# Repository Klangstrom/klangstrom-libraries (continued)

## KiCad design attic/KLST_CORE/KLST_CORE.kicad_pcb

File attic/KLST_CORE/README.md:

# KLANGSTROM / KLST_CORE

KLST_CORE is the core audio processing unit:

- featuring *KLANGSTROM* library
- programmable in Arduino IDE via USB ( *DFUse Mode* )
- debugging + communication via *virtual USB Serial Port*

## feature list (20210303)

- STM32H743 MCU with 480MHz, 1 MB RAM, 2MB Flash
- WM8731 Audio Codec with 2× AUDIO DAC + 2× AUDIO ADC ( 24BIT )
- 16× GPIO Pins
- 6× ADC ( 16BIT )
- 2× DAC ( 12BIT )
- 3× UART ( with symetric IDC )
- 3× I2C ( with symetric IDC )
- 3× SPI ( with symetric IDC )
- 1× SD CARD reader
- USB Host
- USB Device ( + Power Supply )
- 3× Rotary Encoder + Push Button
- 2× Push Buttons
- Reset + Boot Flash + Programmer Buttons
- JTAG/SWD Interface ( 10-Pin )
- Eurorack Power Supply ( 12V )
- Eurorack Connectors for 2× AUDIO DAC + 2× AUDIO ADC 
- 3× programmable LEDs + 1× Power LED
- 4× Mounting Holes

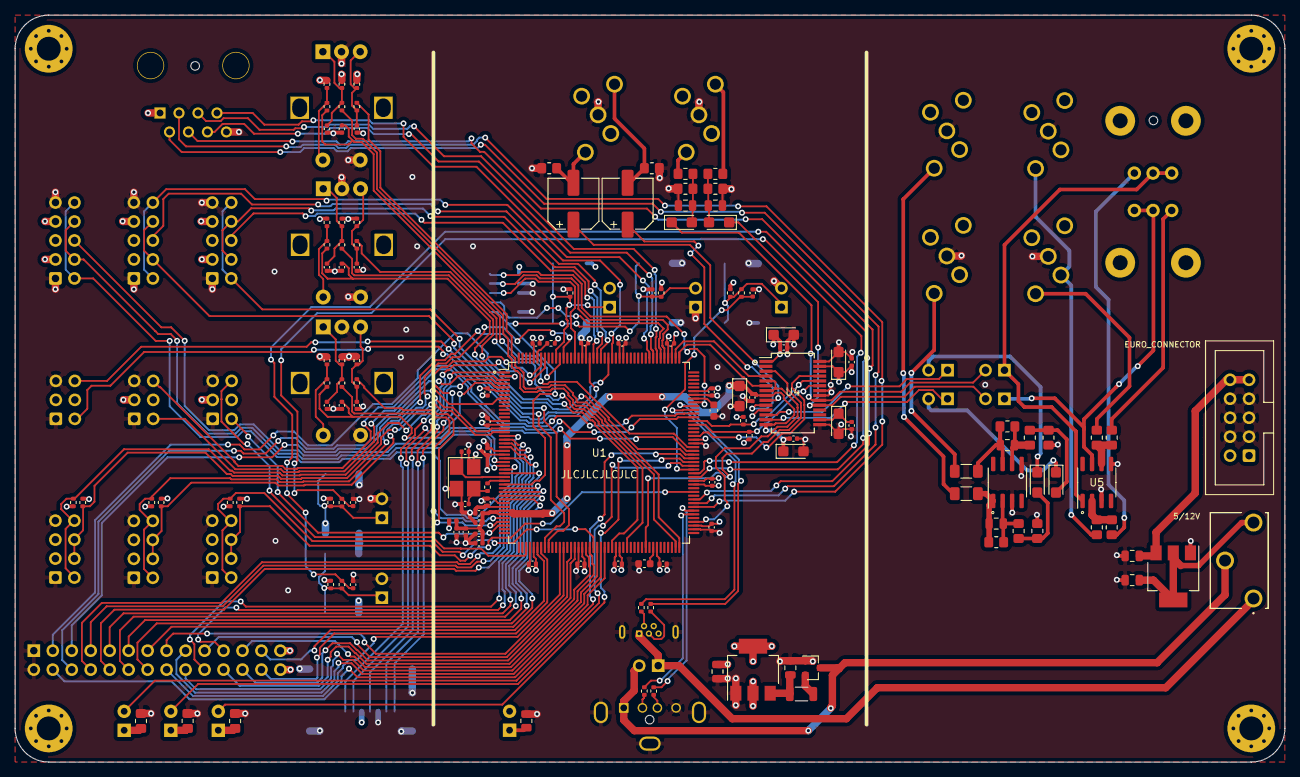
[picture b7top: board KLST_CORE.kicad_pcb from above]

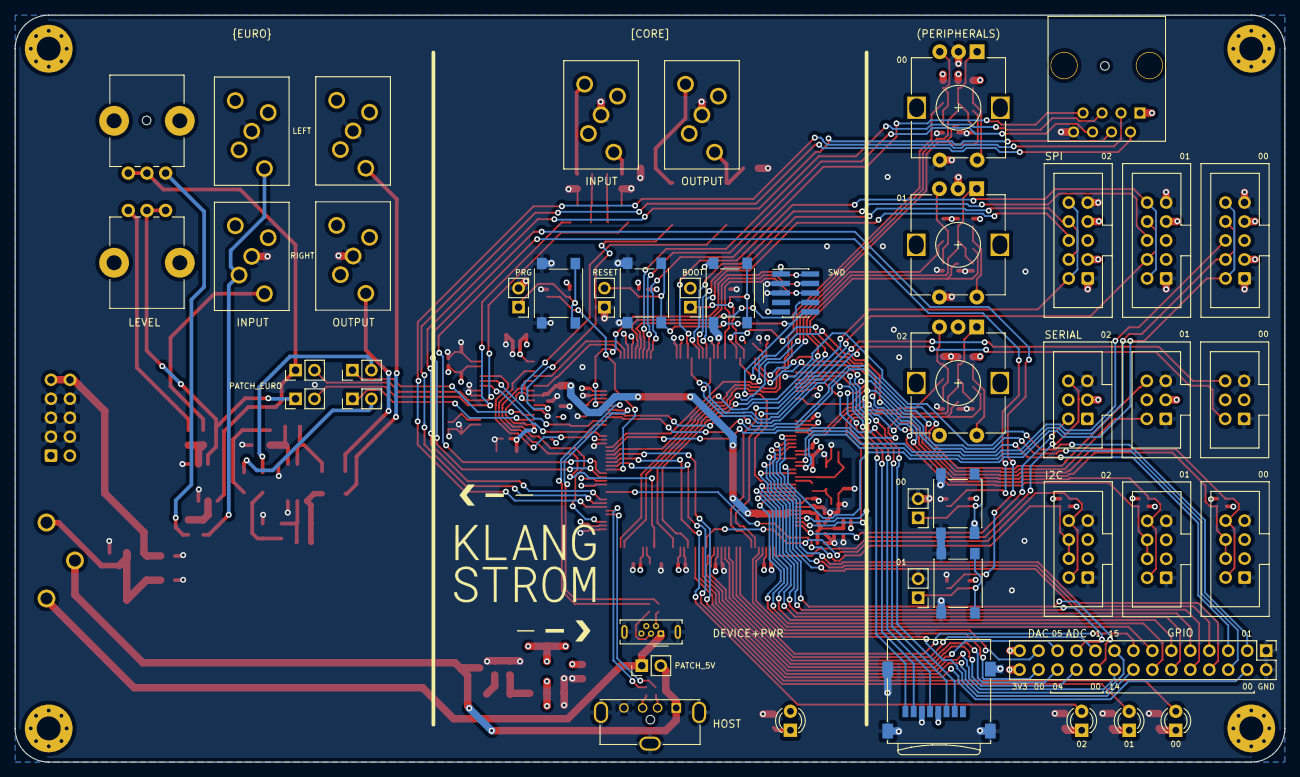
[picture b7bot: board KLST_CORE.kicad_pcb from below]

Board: 4 copper layers, 170.0 x 100.0 mm, 186 parts (46 on the bottom side), 154 nets.

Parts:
C1, C2, C3, C4, C14, C16, C20, C21, C22, C23, C24, C25, C26, C27, C28, C29, C30, C31, C32, C33, C37, C41, C43, C45, C47, C54, C55, C56, C57, C58, C59, C60, C61, C62: 100nF; C_0402_1005Metric
C5, C6, C7, C8: 10uF; C_0805_2012Metric
C9, C10: 12pF; C_0402_1005Metric
C11, C12: 2.2uF; C_0603_1608Metric
C13, C15, C17, C19: 1uF; C_0402_1005Metric
C18: 10nF; C_0402_1005Metric
C34, C35: 220uF; CP_Elec_6.3x5.4
C36, C42, C44, C46, C48, C51, C53: 10uF; CP_EIA-3216-18_Kemet-A
C38, C40: 1uF; CP_EIA-3216-18_Kemet-A
C39, C49: 220pF; C_0805_2012Metric
C50, C52: 18pF; C_0805_2012Metric
D1, D2, D3, D4: LED; LED_D3.0mm
FB1: 600Ω@100MHz; L_1206_3216Metric
H1, H2, H3, H4: MountingHole; MountingHole_3.2mm_M3_Pad_Via
J1: RJ45; RJ45_molex_95503-2884-8P8C_Vertical
J2: Micro_SD_Card; microSD_HC_Wuerth_693072010801
J3: USB_A; USB_A_Molex_105057_Vertical
J4: USB_B_Micro; USB_Micro-B_Wuerth_614105150721_Vertical
J5: GPIO+ANALOG_IO_PINS; PinHeader_2x14_P2.54mm_Vertical
J8: EURORACK_POWER_SUPPLY; IDC-Header_2x05_P2.54mm_Vertical
J9: ARM_JTAG_SWD; PinHeader_2x05_P1.27mm_Vertical_SMD
J10: HEADPHONE_OUT; STX36805NB
J11: LINE_IN; STX36805NB
J12: EURO_IN_RIGHT; STX36805NB
J13: EURO_OUT_RIGHT; STX36805NB
J14: EURO_IN_LEFT; STX36805NB
J15: EURO_OUT_LEFT; STX36805NB
J16: SPI_00; IDC-Header_2x05_P2.54mm_Vertical
J17: UART_00; IDC-Header_2x03_P2.54mm_Vertical
J18: I2C_00; IDC-Header_2x04_P2.54mm_Vertical
J19: UART_01; IDC-Header_2x03_P2.54mm_Vertical
J20: SPI_01; IDC-Header_2x05_P2.54mm_Vertical
J21: I2C_01; IDC-Header_2x04_P2.54mm_Vertical
J22: UART_02; IDC-Header_2x03_P2.54mm_Vertical
J23: SPI_02; IDC-Header_2x05_P2.54mm_Vertical
J24: I2C_02; IDC-Header_2x04_P2.54mm_Vertical
JP1: BUTTON_BOOT_FLASH_EXT; PinHeader_1x02_P2.54mm_Vertical
JP2: BUTTON_RESET_EXT; PinHeader_1x02_P2.54mm_Vertical
JP3: BUTTON_USER_00_EXT; PinHeader_1x02_P2.54mm_Vertical
JP4: BUTTON_USER_01_EXT; PinHeader_1x02_P2.54mm_Vertical
JP5: BUTTON_PROGRAMMER_EXT; PinHeader_1x02_P2.54mm_Vertical
JP6: USB_POWER_INPUT; PinHeader_1x02_P2.54mm_Vertical
JP7: JUMPER_SIGNAL_IN_RIGHT; PinHeader_1x02_P2.54mm_Vertical
JP8: JUMPER_SIGNAL_OUT_RIGHT; PinHeader_1x02_P2.54mm_Vertical
JP9: JUMPER_SIGNAL_IN_LEFT; PinHeader_1x02_P2.54mm_Vertical
JP10: JUMPER_SIGNAL_OUT_LEFT; PinHeader_1x02_P2.54mm_Vertical
L1: 39nH; L_0402_1005Metric
Q1: AO3401A; SOT-23
R1, R2, R3, R4: 22R; R_0402_1005Metric
R5, R6, R7: 1K; R_0805_2012Metric_Pad1.20x1.40mm_HandSolder
R8: 1K; R_0805_2012Metric
R9, R10, R11, R12, R16, R39, R41, R42, R43, R44, R45, R47, R48, R49, R50, R51, R53, R54, R55, R56: 10K; R_0402_1005Metric
R13, R14, R15, R40, R46, R52: 1K; R_0402_1005Metric
R17: 10R; R_0402_1005Metric
R18: 5.6K; R_0402_1005Metric
R19, R20, R57, R58, R59, R60, R61, R62: 2.2K; R_0402_1005Metric
R21, R22: 47K; R_0805_2012Metric_Pad1.20x1.40mm_HandSolder
R23, R24, R25, R26, R30, R36: 5.6K; R_0805_2012Metric_Pad1.20x1.40mm_HandSolder
R27, R33: 3.3K; R_0805_2012Metric_Pad1.20x1.40mm_HandSolder
R28, R32, R34, R38: 39K; R_0805_2012Metric_Pad1.20x1.40mm_HandSolder
R29, R35: 22K; R_0805_2012Metric_Pad1.20x1.40mm_HandSolder
R31, R37: 1K; R_1206_3216Metric_Pad1.30x1.75mm_HandSolder
RV1, RV2: 50K; Potentiometer_Bourns_PTV09A-1_Single_Vertical
SW1: BUTTON_BOOT_FLASH; SW_Push_1P1T_NO_6x6mm_H9.5mm
SW2: BUTTON_RESET; SW_Push_1P1T_NO_6x6mm_H9.5mm
SW3: BUTTON_USER_00; SW_Push_1P1T_NO_6x6mm_H9.5mm
SW4: BUTTON_USER_01; SW_Push_1P1T_NO_6x6mm_H9.5mm
SW5: BUTTON_PROGRAMMER; SW_Push_1P1T_NO_6x6mm_H9.5mm
SW6: POWER_SELECTOR; G1070513
SW7, SW8, SW9: ENCODER; RotaryEncoder_Alps_EC12E-Switch_Vertical_H20mm
U1: STM32H743IITx; LQFP-176_24x24mm_P0.5mm
U2: AMS1117-5.0; SOT-223-3_TabPin2
U3: AMS1117-3.3; SOT-223-3_TabPin2
U4: WM8731SEDS; SSOP-28_5.3x10.2mm_P0.65mm
U5, U6: TL072; SOIC-8_3.9x4.9mm_P1.27mm
X1: LOGO; KLST_CORE--graphics
Y1: 16MHz; Crystal_SMD_3225-4Pin_3.2x2.5mm_HandSoldering

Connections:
+3.3VA: C13.1, C14.1, C15.1, C16.1, C17.1, C18.1, C41.2, C42.1, C43.2, C44.1, L1.2, U1.38, U1.39, U4.8, U4.14
+3V3: C8.1, C19.1, C20.1, C21.1, C22.1, C23.1, C24.1, C25.1, C26.1, C27.1, C28.1, C29.1, C30.1, C31.1, C32.1, C33.1, C45.2, C46.1, C47.2, C48.1, D4.2, J1.1, J2.4, J5.27, J5.28, J9.1, J16.3, J16.7, J17.3, J18.3, J18.5, J19.3, J20.3, J20.7, J21.3, J21.5, J22.3, J23.3, J23.7, J24.3, J24.5, JP1.2, L1.1, R9.2, R10.2, R11.2, R12.2, R18.1, R19.1, R20.1, R39.2, R41.1, R42.1, R45.2, R47.1, R48.1, R51.2, R53.1, R54.1, R57.1, R58.1, R59.1, R60.1, R61.1, R62.1, SW1.2, U1.6, U1.15, U1.23, U1.36, U1.49, U1.62, U1.72, U1.82, U1.91, U1.103, U1.114, U1.127, U1.136, U1.149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
+5V: J3.1, JP6.2, Q1.3, SW6.2
+12V: C5.1, J8.9, J8.10, U2.3
/ADC_00: J5.20, U1.21
/ADC_01: J5.19, U1.59
/ADC_02: J5.22, U1.63
/ADC_03: J5.21, U1.24
/ADC_04: J5.24, U1.60
/ADC_05: J5.23, U1.64
/AUDIOCODEC_I2C_SCL: R19.2, U1.119, U4.24
/AUDIOCODEC_I2C_SDA: R20.2, U1.118, U4.23
/AUDIOCODEC_I2S_CK: U1.79, U4.3
/AUDIOCODEC_I2S_MCK: U1.115, U4.25
/AUDIOCODEC_I2S_SDI: U1.133, U4.6
/AUDIOCODEC_I2S_SDO: U1.134, U4.4
/AUDIOCODEC_I2S_WS: U1.92, U4.5, U4.7
/BOOT_FLASH: JP1.1, R16.2, SW1.1, U1.166
/BUTTON_PROGRAMMER: C3.1, R15.1, U1.106
/BUTTON_USER_00: C1.2, R13.1, U1.105
/BUTTON_USER_01: C2.1, R14.1, U1.104
/DAC_00: J5.26, U1.51
/DAC_01: J5.25, U1.50
/ENCODER_00_A: R49.2, U1.87
/ENCODER_00_B: R50.1, U1.88
/ENCODER_00_BUTTON: C57.1, R46.1, U1.112
/ENCODER_01_A: R43.2, U1.70
/ENCODER_01_B: R44.1, U1.74
/ENCODER_01_BUTTON: C54.1, R40.1, U1.110
/ENCODER_02_A: R55.2, U1.40
/ENCODER_02_B: R56.1, U1.41
/ENCODER_02_BUTTON: C60.1, R52.1, U1.111
/GPIO_00: J5.4, U1.68
/GPIO_01: J5.3, U1.2
/GPIO_02: J5.6, U1.3
/GPIO_03: J5.5, U1.8
/GPIO_04: J5.8, U1.18
/GPIO_05: J5.7, U1.19
/GPIO_06: J5.10, U1.20
/GPIO_07: J5.9, U1.28
/GPIO_08: J5.12, U1.32
/GPIO_09: J5.11, U1.33
/GPIO_10: J5.14, U1.34
/GPIO_11: J5.13, U1.35
/GPIO_12: J5.16, U1.56
/GPIO_13: J5.15, U1.57
/GPIO_14: J5.18, U1.66
/GPIO_15: J5.17, U1.67
/I2C_00_SCL: J18.4, J18.6, R57.2, U1.17
/I2C_00_SDA: J18.2, J18.8, R58.2, U1.16
/I2C_01_SCL: J21.4, J21.6, R59.2, U1.164
/I2C_01_SDA: J21.2, J21.8, R60.2, U1.165
/I2C_02_SCL: J24.4, J24.6, R61.2, U1.100
/I2C_02_SDA: J24.2, J24.8, R62.2, U1.65
/LED_00: D1.2, U1.109
/LED_01: D2.2, U1.107
/LED_02: D3.2, U1.108
/PDR_ON: R18.2, U1.171
/RCC_OSC_IN: C9.2, U1.29, Y1.1
/RCC_OSC_OUT: R17.1, U1.30
/RJ45_GPIO: J1.4, U1.98
/RJ45_SPI_MISO: J1.6, U1.140
/RJ45_SPI_MOSI: J1.7, U1.141
/RJ45_SPI_SCK: J1.5, U1.139
/RJ45_UART_RX: J1.2, U1.97
/RJ45_UART_TX: J1.3, U1.96
/SDCARD_CS: J2.2, U1.169
/SDCARD_DETECT_SDIO: J2.8, U1.170
/SDCARD_MISO: J2.7, U1.4
/SDCARD_MOSI: J2.3, U1.5
/SDCARD_SCK: J2.5, U1.1
/SPI_00_MISO: J16.4, J16.8, U1.26
/SPI_00_MOSI: J16.2, J16.10, U1.27
/SPI_00_SCK: J16.6, U1.25
/SPI_01_MISO: J20.4, J20.8, U1.52
/SPI_01_MOSI: J20.2, J20.10, U1.151
/SPI_01_SCK: J20.6, U1.154
/SPI_02_MISO: J23.4, J23.8, U1.155
/SPI_02_MOSI: J23.2, J23.10, U1.53
/SPI_02_SCK: J23.6, U1.156
/SWD_NRST: C4.2, J9.10, JP2.2, R12.1, SW2.2, U1.31
/SWD_SWCLK: J9.4, U1.137
/SWD_SWDIO: J9.2, U1.124
/SWD_SWI: J9.8, U1.138
/SWD_SWO: J9.6, U1.161
/USART_00_RX: J17.6, U1.152
/USART_00_TX: J17.2, U1.157
/USART_01_RX: J19.6, U1.121
/USART_01_TX: J19.2, U1.120
/USART_02_RX: J22.6, U1.47
/USART_02_TX: J22.2, U1.42
/USB_DEVICE_D+: R2.1, U1.123
/USB_DEVICE_D-: R4.1, U1.122
/USB_HOST_D+: R1.1, U1.95
/USB_HOST_D-: R3.1, U1.94
/USB_POWER_INPUT_5V+: J4.1, JP6.1, SW6.1
/VCAP1: C11.1, U1.81
/VCAP2: C12.1, U1.125
/audio_codec_WM8731/AUDIO_IN_LEFT: J11.T, R23.2
/audio_codec_WM8731/AUDIO_IN_RIGHT: J11.R, R25.2
/audio_codec_WM8731/AUDIO_OUT_LEFT: C34.2, J10.T, R21.1
/audio_codec_WM8731/AUDIO_OUT_RIGHT: C35.2, J10.R, R22.1
/audio_codec_WM8731/HEADPHONE_OUT_LEFT: C34.1, U4.9
/audio_codec_WM8731/HEADPHONE_OUT_RIGHT: C35.1, U4.10
/audio_codec_WM8731/SIGNAL_IN_LEFT: C38.1, JP9.2, U4.20
/audio_codec_WM8731/SIGNAL_IN_RIGHT: C40.1, JP7.2, U4.19
/audio_codec_WM8731/SIGNAL_OUT_LEFT: JP10.1, U4.12
/audio_codec_WM8731/SIGNAL_OUT_RIGHT: JP8.1, U4.13
GND: C1.1, C2.2, C3.2, C4.1, C5.2, C6.2, C7.2, C8.2, C9.1, C10.2, C11.2, C12.2, C13.2, C14.2, C15.2, C16.2, C17.2, C18.2, C19.2, C20.2, C21.2, C22.2, C23.2, C24.2, C25.2, C26.2, C27.2, C28.2, C29.2, C30.2, C31.2, C32.2, C33.2, C36.2, C37.2, C39.1, C41.1, C42.2, C43.1, C44.2, C45.1, C46.2, C47.1, C48.2, C49.1, C54.2, C55.2, C56.2, C57.2, C58.2, C59.2, C60.2, C61.2, C62.2, J1.8, J2.6, J2.9, J3.4, J3.5, J4.5, J4.6, J5.1, J5.2, J8.3, J8.4, J8.5, J8.6, J8.7, J8.8, J9.3, J9.5, J9.9, J10.S, J11.S, J12.S, J13.S, J14.S, J15.S, J16.1, J16.9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
unnamed: C6.1, SW6.3, U2.2
unnamed: C7.1, FB1.1, U3.3
unnamed: C10.1, R17.2, Y1.3
unnamed: C36.1, C37.1, U4.16
unnamed: C38.2, C39.2, R23.1, R24.1
unnamed: C40.2, C49.2, R25.1, R26.1
unnamed: C50.1, R28.2, R31.1, U6.7
unnamed: C50.2, R28.1, R30.2, U6.6
unnamed: C51.1, JP8.2
unnamed: C51.2, R30.1, R32.1
unnamed: C52.1, R34.1, R37.1, U6.1
unnamed: C52.2, R34.2, R36.2, U6.2
unnamed: C53.1, JP10.2
unnamed: C53.2, R36.1, R38.1
unnamed: C55.1, R42.2, R43.1, SW7.A
unnamed: C56.1, R41.2, R44.2, SW7.B
unnamed: C58.1, R48.2, R49.1, SW8.A
unnamed: C59.1, R47.2, R50.2, SW8.B
unnamed: C61.1, R54.2, R55.1, SW9.A
unnamed: C62.1, R53.2, R56.2, SW9.B
unnamed: D1.1, R5.2
unnamed: D2.1, R6.2
unnamed: D3.1, R7.2
unnamed: D4.1, R8.2
unnamed: FB1.2, Q1.2
unnamed: J3.2, R3.2
unnamed: J3.3, R1.2
unnamed: J4.2, R4.2
unnamed: J4.3, R2.2
unnamed: J12.T, R29.2
unnamed: J12.TN, J14.T, R35.2
unnamed: J13.T, R31.2
unnamed: J15.T, R37.2
unnamed: JP3.1, R9.1, R13.2, SW3.2
unnamed: JP4.1, R10.1, R14.2, SW4.2
unnamed: JP5.1, R11.1, R15.2, SW5.2
unnamed: JP7.1, RV1.2, RV1.3, U5.7
unnamed: JP9.1, RV2.2, RV2.3, U5.1
unnamed: R27.1, R29.1, U5.6
unnamed: R27.2, RV1.1
unnamed: R33.1, R35.1, U5.2
unnamed: R33.2, RV2.1
unnamed: R39.1, R40.2, SW7.S1
unnamed: R45.1, R46.2, SW8.S1
unnamed: R51.1, R52.2, SW9.S1

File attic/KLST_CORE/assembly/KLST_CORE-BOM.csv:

Comment,Designator,Footprint,LCSC
"2.2uF","C11,C12","Capacitor_SMD:C_0603_1608Metric","C23630"
"1uF","C13,C15,C17,C19","Capacitor_SMD:C_0402_1005Metric","C52923"
"100nF","C1,C2,C3,C4,C14,C16,C20,C21,C22,C23,C24,C25,C26,C27,C28,C29,C30,C31,C32,C33,C37,C41,C43,C45,C47,C54,C55,C56,C57,C58,C59,C60,C61,C62","Capacitor_SMD:C_0402_1005Metric","C1525"
"10nF","C18","Capacitor_SMD:C_0402_1005Metric","C15195"
"220uF","C34,C35","Capacitor_SMD:CP_Elec_6.3x5.4","C3345"
"10uF","C36,C42,C44,C46,C48,C51,C53","Capacitor_Tantalum_SMD:CP_EIA-3216-18_Kemet-A","C7171"
"1uF","C38,C40","Capacitor_Tantalum_SMD:CP_EIA-3216-18_Kemet-A","C7175"
"220pF","C39,C49","Capacitor_SMD:C_0805_2012Metric","C53172"
"18pF","C50,C52","Capacitor_SMD:C_0805_2012Metric","C1797"
"10uF","C5,C6,C7,C8","Capacitor_SMD:C_0805_2012Metric","C15850"
"12pF","C9,C10","Capacitor_SMD:C_0402_1005Metric","C1547"
"LED","D1,D2,D3,D4","LED_THT:LED_D3.0mm","C34499"
"600Ω@100MHz","FB1","Inductor_SMD:L_1206_3216Metric","C73732"
"MountingHole","H1,H2,H3,H4","MountingHole:MountingHole_3.2mm_M3_Pad_Via",""
"RJ45","J1","Connector_RJ:RJ45_molex_95503-2884-8P8C_Vertical",""
"HEADPHONE_OUT","J10","KLST_CORE:STX36805NB",""
"LINE_IN","J11","KLST_CORE:STX36805NB",""
"EURO_IN_RIGHT","J12","KLST_CORE:STX36805NB",""
"EURO_OUT_RIGHT","J13","KLST_CORE:STX36805NB",""
"EURO_IN_LEFT","J14","KLST_CORE:STX36805NB",""
"EURO_OUT_LEFT","J15","KLST_CORE:STX36805NB",""
"SPI_00","J16","Connector_IDC:IDC-Header_2x05_P2.54mm_Vertical",""
"UART_00","J17","Connector_IDC:IDC-Header_2x03_P2.54mm_Vertical",""
"I2C_00","J18","Connector_IDC:IDC-Header_2x04_P2.54mm_Vertical",""
"UART_01","J19","Connector_IDC:IDC-Header_2x03_P2.54mm_Vertical",""
"Micro_SD_Card","J2","Connector_Card:microSD_HC_Wuerth_693072010801",""
"SPI_01","J20","Connector_IDC:IDC-Header_2x05_P2.54mm_Vertical",""
"I2C_01","J21","Connector_IDC:IDC-Header_2x04_P2.54mm_Vertical",""
"UART_02","J22","Connector_IDC:IDC-Header_2x03_P2.54mm_Vertical",""
"SPI_02","J23","Connector_IDC:IDC-Header_2x05_P2.54mm_Vertical",""
"I2C_02","J24","Connector_IDC:IDC-Header_2x04_P2.54mm_Vertical",""
"USB_A","J3","Connector_USB:USB_A_Molex_105057_Vertical",""
"USB_B_Micro","J4","Connector_USB:USB_Micro-B_Wuerth_614105150721_Vertical",""
"GPIO+ANALOG_IO_PINS","J5","Connector_PinHeader_2.54mm:PinHeader_2x14_P2.54mm_Vertical",""
"EURORACK_POWER_SUPPLY","J8","Connector_IDC:IDC-Header_2x05_P2.54mm_Vertical",""
"ARM_JTAG_SWD","J9","Connector_PinHeader_1.27mm:PinHeader_2x05_P1.27mm_Vertical_SMD",""
"BUTTON_BOOT_FLASH_EXT","JP1","Connector_PinHeader_2.54mm:PinHeader_1x02_P2.54mm_Vertical",""
"JUMPER_SIGNAL_OUT_LEFT","JP10","Connector_PinHeader_2.54mm:PinHeader_1x02_P2.54mm_Vertical",""
"BUTTON_RESET_EXT","JP2","Connector_PinHeader_2.54mm:PinHeader_1x02_P2.54mm_Vertical",""
"BUTTON_USER_00_EXT","JP3","Connector_PinHeader_2.54mm:PinHeader_1x02_P2.54mm_Vertical",""
"BUTTON_USER_01_EXT","JP4","Connector_PinHeader_2.54mm:PinHeader_1x02_P2.54mm_Vertical",""
"BUTTON_PROGRAMMER_EXT","JP5","Connector_PinHeader_2.54mm:PinHeader_1x02_P2.54mm_Vertical",""
"USB_POWER_INPUT","JP6","Connector_PinHeader_2.54mm:PinHeader_1x02_P2.54mm_Vertical",""
"JUMPER_SIGNAL_IN_RIGHT","JP7","Connector_PinHeader_2.54mm:PinHeader_1x02_P2.54mm_Vertical",""
"JUMPER_SIGNAL_OUT_RIGHT","JP8","Connector_PinHeader_2.54mm:PinHeader_1x02_P2.54mm_Vertical",""
"JUMPER_SIGNAL_IN_LEFT","JP9","Connector_PinHeader_2.54mm:PinHeader_1x02_P2.54mm_Vertical",""
"39nH","L1","Inductor_SMD:L_0402_1005Metric","C26443"
"AO3401A","Q1","Package_TO_SOT_SMD:SOT-23","C15127"
"10K","R9,R10,R11,R12,R16,R39,R41,R42,R43,R44,R45,R47,R48,R49,R50,R51,R53,R54,R55,R56","Resistor_SMD:R_0402_1005Metric","C25744"
"1K","R13,R14,R15,R40,R46,R52","Resistor_SMD:R_0402_1005Metric","C11702"
"10R","R17","Resistor_SMD:R_0402_1005Metric","C25077"
"5.6K","R18","Resistor_SMD:R_0402_1005Metric","C25908"
"2.2K","R19,R20,R57,R58,R59,R60,R61,R62","Resistor_SMD:R_0402_1005Metric","C25879"
"47K","R21,R22","Resistor_SMD:R_0805_2012Metric_Pad1.20x1.40mm_HandSolder","C17713"
"5.6K","R23,R24,R25,R26,R30,R36","Resistor_SMD:R_0805_2012Metric_Pad1.20x1.40mm_HandSolder","C4382"
"22K","R29,R35","Resistor_SMD:R_0805_2012Metric_Pad1.20x1.40mm_HandSolder","C17560"
"3.3K","R27,R33","Resistor_SMD:R_0805_2012Metric_Pad1.20x1.40mm_HandSolder","C26010"
"1K","R31,R37","Resistor_SMD:R_1206_3216Metric_Pad1.30x1.75mm_HandSolder","C4410"
"39K","R28,R32,R34,R38","Resistor_SMD:R_0805_2012Metric_Pad1.20x1.40mm_HandSolder","C25826"
"22R","R1,R2,R3,R4","Resistor_SMD:R_0402_1005Metric","C25092"
"1K","R5,R6,R7","Resistor_SMD:R_0805_2012Metric_Pad1.20x1.40mm_HandSolder","C17513"
"1K","R8","Resistor_SMD:R_0805_2012Metric","C17513"
"50K","RV1,RV2","Potentiometer_THT:Potentiometer_Bourns_PTV09A-1_Single_Vertical",""
"BUTTON_BOOT_FLASH","SW1","Button_Switch_SMD:SW_Push_1P1T_NO_6x6mm_H9.5mm",""
"BUTTON_RESET","SW2","Button_Switch_SMD:SW_Push_1P1T_NO_6x6mm_H9.5mm",""
"BUTTON_USER_00","SW3","Button_Switch_SMD:SW_Push_1P1T_NO_6x6mm_H9.5mm",""
"BUTTON_USER_01","SW4","Button_Switch_SMD:SW_Push_1P1T_NO_6x6mm_H9.5mm",""
"BUTTON_PROGRAMMER","SW5","Button_Switch_SMD:SW_Push_1P1T_NO_6x6mm_H9.5mm",""
"POWER_SELECTOR","SW6","KLST_CORE:G1070513",""
"ENCODER","SW7,SW8,SW9","Rotary_Encoder:RotaryEncoder_Alps_EC12E-Switch_Vertical_H20mm",""
"STM32H743IITx","U1","Package_QFP:LQFP-176_24x24mm_P0.5mm","C89597"
"AMS1117-5.0","U2","Package_TO_SOT_SMD:SOT-223-3_TabPin2","C6187"
"AMS1117-3.3","U3","Package_TO_SOT_SMD:SOT-223-3_TabPin2","C6186"
"WM8731SEDS","U4","Package_SO:SSOP-28_5.3x10.2mm_P0.65mm","C323837"
"TL072","U5,U6","Package_SO:SOIC-8_3.9x4.9mm_P1.27mm","C6961"
"KLST_CORE--graphics","X1","KLST_CORE:KLST_CORE--graphics",""
"16MHz","Y1","Crystal:Crystal_SMD_3225-4Pin_3.2x2.5mm_HandSoldering","C13738"

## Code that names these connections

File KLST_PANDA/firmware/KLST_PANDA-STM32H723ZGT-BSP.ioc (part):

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Mcu.Name=STM32H723ZGTx
Mcu.Package=LQFP144
Mcu.UserName=STM32H723ZGTx
PA0.GPIOParameters=GPIO_Label
PA0.GPIO_Label=_ENCODER_01_A
PA0.Signal=S_TIM2_CH1_ETR
PA1.GPIOParameters=GPIO_Label
PA1.GPIO_Label=_ENCODER_01_B
PA1.Signal=S_TIM2_CH2
PA10.GPIOParameters=GPIO_Label
PA10.GPIO_Label=_ENCODER_00_BUTTON
PA10.Signal=S_TIM1_CH3
PA11.GPIOParameters=GPIO_Label
PA11.GPIO_Label=_USB_DEVICE_HOST_MINUS
PA11.Mode=Host_FS
PA11.Signal=USB_OTG_HS_DM
PA12.GPIOParameters=GPIO_Label
PA12.GPIO_Label=_USB_DEVICE_HOST_PLUS
PA12.Mode=Host_FS
PA12.Signal=USB_OTG_HS_DP
PA13(JTMS/SWDIO).GPIOParameters=GPIO_Label
PA13(JTMS/SWDIO).GPIO_Label=_SWD_IO
PA13(JTMS/SWDIO).Mode=Trace_Asynchronous_SW
PA13(JTMS/SWDIO).Signal=DEBUG_JTMS-SWDIO
PA14(JTCK/SWCLK).GPIOParameters=GPIO_Label
PA14(JTCK/SWCLK).GPIO_Label=_SWD_CLK
PA14(JTCK/SWCLK).Mode=Trace_Asynchronous_SW
PA14(JTCK/SWCLK).Signal=DEBUG_JTCK-SWCLK
PA15(JTDI).GPIOParameters=GPIO_Speed,GPIO_Label
PA15(JTDI).GPIO_Label=_DISPLAY_LTDC_R3
PA15(JTDI).GPIO_Speed=GPIO_SPEED_FREQ_VERY_HIGH
PA15(JTDI).Mode=RGB888
PA15(JTDI).Signal=LTDC_R3
PA2.GPIOParameters=GPIO_Speed,GPIO_Label
PA2.GPIO_Label=_DISPLAY_LTDC_R1
PA2.GPIO_Speed=GPIO_SPEED_FREQ_VERY_HIGH
PA2.Mode=RGB888
PA2.Signal=LTDC_R1
PA3.GPIOParameters=GPIO_Label
PA3.GPIO_Label=SERIAL_USR_RX
PA3.Mode=Asynchronous
PA3.Signal=USART2_RX
PA4.GPIOParameters=GPIO_Label
PA4.GPIO_Label=_DAC_USR
PA4.Signal=COMP_DAC11_group
PA5.GPIOParameters=GPIO_Speed,GPIO_Label
PA5.GPIO_Label=_DISPLAY_LTDC_R4
PA5.GPIO_Speed=GPIO_SPEED_FREQ_VERY_HIGH
PA5.Mode=RGB888
PA5.Signal=LTDC_R4
PA6.GPIOParameters=GPIO_Speed,GPIO_Label
PA6.GPIO_Label=_DISPLAY_LTDC_G2
PA6.GPIO_Speed=GPIO_SPEED_FREQ_VERY_HIGH
PA6.Mode=RGB888
PA6.Signal=LTDC_G2
PA7.GPIOParameters=GPIO_Speed,GPIO_Label
PA7.GPIO_Label=_DISPLAY_LTDC_VSYNC
PA7.GPIO_Speed=GPIO_SPEED_FREQ_VERY_HIGH
PA7.Mode=RGB888
PA7.Signal=LTDC_VSYNC
PA8.GPIOParameters=GPIO_Label
PA8.GPIO_Label=_ENCODER_00_A
PA8.Signal=S_TIM1_CH1
PA9.GPIOParameters=GPIO_Label
PA9.GPIO_Label=_USB_DEVICE_HOST_VBUS
PA9.Mode=Activate_VBUS_FS
PA9.Signal=USB_OTG_HS_VBUS
PB0.GPIOParameters=GPIO_Speed,GPIO_Label
PB0.GPIO_Label=_DISPLAY_LTDC_G1
PB0.GPIO_Speed=GPIO_SPEED_FREQ_VERY_HIGH
PB0.Mode=RGB888
PB0.Signal=LTDC_G1
PB1.GPIOParameters=GPIO_Speed,GPIO_Label
PB1.GPIO_Label=_DISPLAY_LTDC_G0
PB1.GPIO_Speed=GPIO_SPEED_FREQ_VERY_HIGH
PB1.Mode=RGB888
PB1.Signal=LTDC_G0
PB10.GPIOParameters=GPIO_Speed,GPIO_Label
PB10.GPIO_Label=_DISPLAY_LTDC_G4
PB10.GPIO_Speed=GPIO_SPEED_FREQ_VERY_HIGH
PB10.Mode=RGB888
PB10.Signal=LTDC_G4
PB11.GPIOParameters=GPIO_Label
PB11.GPIO_Label=_ENCODER_01_BUTTON
PB11.Signal=S_TIM2_CH4
PB12.GPIOParameters=GPIO_Label
PB12.GPIO_Label=_EXT_MEMORY_A0
PB12.Mode=OCTOSPI1_IOL_Port1L
PB12.Signal=OCTOSPIM_P1_IO0
PB13.GPIOParameters=GPIO_Label
PB13.GPIO_Label=_EXT_MEMORY_A2
PB13.Mode=OCTOSPI1_IOL_Port1L
PB13.Signal=OCTOSPIM_P1_IO2
PB14.GPIOParameters=GPIO_Label
PB14.GPIO_Label=_LED_00
PB14.Signal=S_TIM12_CH1
PB15.GPIOParameters=GPIO_Label
PB15.GPIO_Label=_LED_01
PB15.Signal=S_TIM12_CH2
PB2.GPIOParameters=GPIO_Speed,GPIO_Label
PB2.GPIO_Label=_AUDIO_CODEC_SAI_SD_IN
PB2.GPIO_Speed=GPIO_SPEED_FREQ_LOW
PB2.Mode=SAI_A_SyncSlave
PB2.Signal=SAI1_SD_A
PB3(JTDO/TRACESWO).GPIOParameters=GPIO_Label
PB3(JTDO/TRACESWO).GPIO_Label=_SWD_OUT
PB3(JTDO/TRACESWO).Mode=Trace_Asynchronous_SW
PB3(JTDO/TRACESWO).Signal=DEBUG_JTDO-SWO
PB4(NJTRST).GPIOParameters=GPIO_Label
PB4(NJTRST).GPIO_Label=GPIO_11
PB4(NJTRST).Signal=GPIO_Output
PB5.GPIOParameters=GPIO_Speed,GPIO_Label
PB5.GPIO_Label=_DISPLAY_LTDC_B5
PB5.GPIO_Speed=GPIO_SPEED_FREQ_VERY_HIGH
PB5.Mode=RGB888
PB5.Signal=LTDC_B5
PB6.GPIOParameters=GPIO_Label
PB6.GPIO_Label=I2C_USR_SCL
PB6.Mode=I2C
PB6.Signal=I2C1_SCL
PB7.GPIOParameters=GPIO_Label
PB7.GPIO_Label=I2C_USR_SDA
PB7.Mode=I2C
PB7.Signal=I2C1_SDA
PB8.GPIOParameters=GPIO_Speed,GPIO_Label
PB8.GPIO_Label=_DISPLAY_LTDC_B6
PB8.GPIO_Speed=GPIO_SPEED_FREQ_VERY_HIGH
PB8.Mode=RGB888
PB8.Signal=LTDC_B6
PB9.GPIOParameters=GPIO_Speed,GPIO_Label
PB9.GPIO_Label=_DISPLAY_LTDC_B7
PB9.GPIO_Speed=GPIO_SPEED_FREQ_VERY_HIGH
PB9.Mode=RGB888
PB9.Signal=LTDC_B7
PC0.GPIOParameters=GPIO_Speed,GPIO_Label
PC0.GPIO_Label=_DISPLAY_LTDC_R5
PC0.GPIO_Speed=GPIO_SPEED_FREQ_VERY_HIGH
PC0.Mode=RGB888
PC0.Signal=LTDC_R5
PC1.GPIOParameters=GPIO_Speed,GPIO_Label
PC1.GPIO_Label=_DISPLAY_LTDC_G5
PC1.GPIO_Speed=GPIO_SPEED_FREQ_VERY_HIGH
PC1.Mode=RGB888
PC1.Signal=LTDC_G5
PC10.GPIOParameters=GPIO_Speed,GPIO_Label
PC10.GPIO_Label=_DISPLAY_LTDC_R2
PC10.GPIO_Speed=GPIO_SPEED_FREQ_VERY_HIGH
PC10.Mode=RGB888
PC10.Signal=LTDC_R2
PC11.GPIOParameters=GPIO_Label
PC11.GPIO_Label=_MIDI_ANALOG_IN
PC11.Mode=Asynchronous
PC11.Signal=UART4_RX
PC12.GPIOParameters=GPIO_Speed,GPIO_Label
PC12.GPIO_Label=_DISPLAY_LTDC_R6
PC12.GPIO_Speed=GPIO_SPEED_FREQ_VERY_HIGH
PC12.Mode=RGB888
PC12.Signal=LTDC_R6
PC13.GPIOParameters=GPIO_Label
PC13.GPIO_Label=GPIO_10
PC13.Signal=GPIO_Output
PC14-OSC32_IN.GPIOParameters=GPIO_Label
PC14-OSC32_IN.GPIO_Label=GPIO_09
PC14-OSC32_IN.Signal=GPIO_Output
PC15-OSC32_OUT.GPIOParameters=GPIO_Label
PC15-OSC32_OUT.GPIO_Label=GPIO_08
PC15-OSC32_OUT.Signal=GPIO_Output
PC2_C.GPIOParameters=GPIO_Label
PC2_C.GPIO_Label=_AUDIO_MIC_CLK
PC2_C.Signal=S_CKOUTDFSDM1
PC3_C.GPIOParameters=GPIO_Label
PC3_C.GPIO_Label=_AUDIO_MIC_DATA
PC3_C.Signal=S_DATAIN1DFSDM1
PC4.GPIOParameters=GPIO_Label
PC4.GPIO_Label=_DISPLAY_ON_OFF
PC4.Signal=GPIO_Output
PC5.GPIOParameters=GPIO_Label
PC5.GPIO_Label=_EXT_MEMORY_DQS
PC5.Mode=OCTOSPI1_Port1_DQS
PC5.Signal=OCTOSPIM_P1_DQS
PC6.GPIOParameters=GPIO_Speed,GPIO_Label
PC6.GPIO_Label=_DISPLAY_LTDC_HSYNC
PC6.GPIO_Speed=GPIO_SPEED_FREQ_VERY_HIGH
PC6.Mode=RGB888
PC6.Signal=LTDC_HSYNC
PC7.GPIOParameters=GPIO_Speed,GPIO_Label
PC7.GPIO_Label=_DISPLAY_LTDC_G6
PC7.GPIO_Speed=GPIO_SPEED_FREQ_VERY_HIGH
PC7.Mode=RGB888
PC7.Signal=LTDC_G6
PC8.GPIOParameters=GPIO_Label
PC8.GPIO_Label=_DISPLAY_BACKLIGHT_PWM
PC8.Signal=S_TIM3_CH3
PC9.GPIOParameters=GPIO_Speed,GPIO_Label
PC9.GPIO_Label=_DISPLAY_LTDC_G3
PC9.GPIO_Speed=GPIO_SPEED_FREQ_VERY_HIGH
PC9.Mode=RGB888
PC9.Signal=LTDC_G3
PD0.GPIOParameters=GPIO_Speed,GPIO_Label
PD0.GPIO_Label=_DISPLAY_LTDC_B1
PD0.GPIO_Speed=GPIO_SPEED_FREQ_VERY_HIGH
PD0.Mode=RGB888
PD0.Signal=LTDC_B1
PD1.GPIOParameters=GPIO_Label
PD1.GPIO_Label=_MIDI_ANALOG_OUT
PD1.Mode=Asynchronous
PD1.Signal=UART4_TX
PD10.GPIOParameters=GPIO_Speed,GPIO_Label
PD10.GPIO_Label=_DISPLAY_LTDC_B3
PD10.GPIO_Speed=GPIO_SPEED_FREQ_VERY_HIGH
PD10.Mode=RGB888
PD10.Signal=LTDC_B3
PD11.GPIOParameters=GPIO_Label
PD11.GPIO_Label=GPIO_06
PD11.Signal=GPIO_Output
PD12.GPIOParameters=GPIO_Label
PD12.GPIO_Label=_EXT_MEMORY_A1
PD12.Mode=OCTOSPI1_IOL_Port1L
PD12.Signal=OCTOSPIM_P1_IO1
PD13.GPIOParameters=GPIO_PuPd,GPIO_Label
PD13.GPIO_Label=_DISPLAY_TOUCH_INTERRUPT
PD13.GPIO_PuPd=GPIO_PULLUP
PD13.Signal=GPXTI13
PD14.GPIOParameters=GPIO_Label,GPIO_ModeDefaultEXTI
PD14.GPIO_Label=_MECH_BUTTON_00
PD14.GPIO_ModeDefaultEXTI=GPIO_MODE_IT_RISING_FALLING
PD14.Signal=GPXTI14
PD15.GPIOParameters=GPIO_Label
PD15.GPIO_Label=_MECH_BUTTON_01
PD15.Signal=S_TIM4_CH4
PD2.GPIOParameters=GPIO_Speed,GPIO_Label
PD2.GPIO_Label=_DISPLAY_LTDC_B2
PD2.GPIO_Speed=GPIO_SPEED_FREQ_VERY_HIGH
PD2.Mode=RGB888
PD2.Signal=LTDC_B2
PD3.GPIOParameters=GPIO_Label
PD3.GPIO_Label=GPIO_18
PD3.Signal=GPIO_Output
PD4.GPIOParameters=GPIO_Label
PD4.GPIO_Label=GPIO_12
PD4.Signal=GPIO_Output
PD5.GPIOParameters=GPIO_Label
PD5.GPIO_Label=SERIAL_USR_TX
PD5.Mode=Asynchronous
PD5.Signal=USART2_TX
PD6.GPIOParameters=GPIO_Label
PD6.GPIO_Label=_CARD_SDMMC_CK
PD6.Mode=SD_4_bits_Wide_bus
PD6.Signal=SDMMC2_CK
PD7.GPIOParameters=GPIO_Label
PD7.GPIO_Label=_CARD_SDMMC_CMD
PD7.Mode=SD_4_bits_Wide_bus
PD7.Signal=SDMMC2_CMD
PD8.GPIOParameters=GPIO_Label
PD8.GPIO_Label=_SERIAL_DEBUG_TX
PD8.Mode=Asynchronous
PD8.Signal=USART3_TX
PD9.GPIOParameters=GPIO_Label
PD9.GPIO_Label=_SERIAL_DEBUG_RX
PD9.Mode=Asynchronous
PD9.Signal=USART3_RX
PE0.GPIOParameters=GPIO_Label
PE0.GPIO_Label=_IDC_SERIAL_00_RX
PE0.Mode=Asynchronous
PE0.Signal=UART8_RX
PE1.GPIOParameters=GPIO_Label
PE1.GPIO_Label=_IDC_SERIAL_00_TX
PE1.Mode=Asynchronous
PE1.Signal=UART8_TX
PE10.GPIOParameters=GPIO_Label
PE10.GPIO_Label=_EXT_MEMORY_A7
PE10.Mode=OCTOSPI1_IOH_Port1H
PE10.Signal=OCTOSPIM_P1_IO7
PE11.GPIOParameters=GPIO_Label
PE11.GPIO_Label=_ENCODER_00_B
PE11.Signal=S_TIM1_CH2
PE12.GPIOParameters=GPIO_Speed,GPIO_Label
PE12.GPIO_Label=_DISPLAY_LTDC_B4
PE12.GPIO_Speed=GPIO_SPEED_FREQ_VERY_HIGH
PE12.Mode=RGB888
PE12.Signal=LTDC_B4
PE13.GPIOParameters=GPIO_Speed,GPIO_Label
PE13.GPIO_Label=_DISPLAY_LTDC_DE
PE13.GPIO_Speed=GPIO_SPEED_FREQ_VERY_HIGH
PE13.Mode=RGB888
PE13.Signal=LTDC_DE
PE14.GPIOParameters=GPIO_Label
PE14.GPIO_Label=GPIO_17
PE14.Signal=GPIO_Output
PE15.GPIOParameters=GPIO_Speed,GPIO_Label
PE15.GPIO_Label=_DISPLAY_LTDC_R7
PE15.GPIO_Speed=GPIO_SPEED_FREQ_VERY_HIGH
PE15.Mode=RGB888
PE15.Signal=LTDC_R7
PE2.GPIOParameters=GPIO_Label
PE2.GPIO_Label=SPI_USR_SCK
PE2.Mode=Full_Duplex_Master
PE2.Signal=SPI4_SCK
PE3.GPIOParameters=GPIO_Speed,GPIO_Label
PE3.GPIO_Label=_AUDIO_CODEC_SAI_SD_OUT
PE3.GPIO_Speed=GPIO_SPEED_FREQ_LOW

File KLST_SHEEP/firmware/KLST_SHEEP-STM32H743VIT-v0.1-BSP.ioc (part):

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Mcu.Name=STM32H743VITx
Mcu.Package=LQFP100
Mcu.UserName=STM32H743VITx
PA0.GPIOParameters=GPIO_Label
PA0.GPIO_Label=ENCODER_00_A
PA0.Signal=S_TIM2_CH1_ETR
PA1.GPIOParameters=GPIO_Label
PA1.GPIO_Label=ENCODER_00_B
PA1.Signal=S_TIM2_CH2
PA10.GPIOParameters=GPIO_Label
PA10.GPIO_Label=ENCODER_01_BUTTON
PA10.Signal=S_TIM1_CH3
PA11.GPIOParameters=GPIO_Label
PA11.GPIO_Label=USB_DEVICE-
PA11.Mode=Device_Only
PA11.Signal=USB_OTG_FS_DM
PA12.GPIOParameters=GPIO_Label
PA12.GPIO_Label=USB_DEVICE+
PA12.Mode=Device_Only
PA12.Signal=USB_OTG_FS_DP
PA13\ (JTMS/SWDIO).GPIOParameters=GPIO_Label
PA13\ (JTMS/SWDIO).GPIO_Label=SWD_SWDIO
PA13\ (JTMS/SWDIO).Mode=Trace_Asynchronous_SW
PA13\ (JTMS/SWDIO).Signal=DEBUG_JTMS-SWDIO
PA14\ (JTCK/SWCLK).GPIOParameters=GPIO_Label
PA14\ (JTCK/SWCLK).GPIO_Label=SWD_SWCLK
PA14\ (JTCK/SWCLK).Mode=Trace_Asynchronous_SW
PA14\ (JTCK/SWCLK).Signal=DEBUG_JTCK-SWCLK
PA15\ (JTDI).GPIOParameters=GPIO_Label
PA15\ (JTDI).GPIO_Label=SPI_DISPLAY_CS
PA15\ (JTDI).Mode=NSS_Signal_Hard_Output
PA15\ (JTDI).Signal=SPI3_NSS
PA2.GPIOParameters=GPIO_Label
PA2.GPIO_Label=LED_15
PA2.Signal=S_TIM15_CH1
PA3.GPIOParameters=GPIO_Label
PA3.GPIO_Label=ENCODER_00_BUTTON
PA3.Signal=S_TIM2_CH4
PA4.GPIOParameters=GPIO_Label
PA4.GPIO_Label=DAC_00
PA4.Signal=COMP_DAC11_group
PA5.GPIOParameters=GPIO_Label
PA5.GPIO_Label=DAC_01
PA5.Signal=COMP_DAC12_group
PA6.GPIOParameters=GPIO_Label
PA6.GPIO_Label=LED_14
PA6.Signal=S_TIM13_CH1
PA7.GPIOParameters=GPIO_Label
PA7.GPIO_Label=LED_13
PA7.Signal=S_TIM14_CH1
PA8.GPIOParameters=GPIO_Label
PA8.GPIO_Label=ENCODER_01_A
PA8.Signal=S_TIM1_CH1
PA9.GPIOParameters=GPIO_Label
PA9.GPIO_Label=ENCODER_01_B
PA9.Signal=S_TIM1_CH2
PB0.GPIOParameters=GPIO_Label
PB0.GPIO_Label=LED_12
PB0.Signal=S_TIM3_CH3
PB1.GPIOParameters=GPIO_Label
PB1.GPIO_Label=LED_11
PB1.Signal=S_TIM3_CH4
PB10.GPIOParameters=GPIO_Label,GPIO_Pu
PB10.GPIO_Label=I2C_USR_SCL
PB10.GPIO_Pu=GPIO_PULLUP
PB10.Mode=I2C
PB10.Signal=I2C2_SCL
PB11.GPIOParameters=GPIO_Label,GPIO_Pu
PB11.GPIO_Label=I2C_USR_SDA
PB11.GPIO_Pu=GPIO_NOPULL
PB11.Mode=I2C
PB11.Signal=I2C2_SDA
PB12.GPIOParameters=GPIO_Label
PB12.GPIO_Label=SDCARD_SPI_CS
PB12.Mode=NSS_Signal_Hard_Output
PB12.Signal=SPI2_NSS
PB13.GPIOParameters=GPIO_Label
PB13.GPIO_Label=SDCARD_SPI_SCK
PB13.Mode=Full_Duplex_Master
PB13.Signal=SPI2_SCK
PB14.GPIOParameters=GPIO_Label
PB14.GPIO_Label=USB_HOST-
PB14.Mode=Host_FS
PB14.Signal=USB_OTG_HS_DM
PB15.GPIOParameters=GPIO_Label
PB15.GPIO_Label=USB_HOST+
PB15.Mode=Host_FS
PB15.Signal=USB_OTG_HS_DP
PB2.GPIOParameters=GPIO_Label
PB2.GPIO_Label=GPIO_11
PB2.Signal=GPIO_Output
PB3\ (JTDO/TRACESWO).GPIOParameters=GPIO_Label
PB3\ (JTDO/TRACESWO).GPIO_Label=SWD_SWO
PB3\ (JTDO/TRACESWO).Mode=Trace_Asynchronous_SW
PB3\ (JTDO/TRACESWO).Signal=DEBUG_JTDO-SWO
PB4\ (NJTRST).GPIOParameters=GPIO_Label
PB4\ (NJTRST).GPIO_Label=LED_02
PB4\ (NJTRST).Signal=S_TIM3_CH1
PB5.GPIOParameters=GPIO_Label
PB5.GPIO_Label=LED_01
PB5.Signal=S_TIM3_CH2
PB6.GPIOParameters=GPIO_Speed,GPIO_Label,GPIO_Pu
PB6.GPIO_Label=AUDIOCODEC_I2C_SCL
PB6.GPIO_Pu=GPIO_PULLUP
PB6.GPIO_Speed=GPIO_SPEED_FREQ_HIGH
PB6.Mode=I2C
PB6.Signal=I2C1_SCL
PB7.GPIOParameters=GPIO_Speed,GPIO_Label,GPIO_Pu
PB7.GPIO_Label=AUDIOCODEC_I2C_SDA
PB7.GPIO_Pu=GPIO_PULLUP
PB7.GPIO_Speed=GPIO_SPEED_FREQ_HIGH
PB7.Mode=I2C
PB7.Signal=I2C1_SDA
PB8.GPIOParameters=GPIO_Label
PB8.GPIO_Label=LED_00
PB8.Signal=S_TIM16_CH1
PB9.GPIOParameters=GPIO_Label
PB9.GPIO_Label=BUTTON_PRG
PB9.Signal=S_TIM17_CH1
PC0.GPIOParameters=GPIO_Label
PC0.GPIO_Label=GPIO_12
PC0.Signal=GPIO_Output
PC1.GPIOParameters=GPIO_Label
PC1.GPIO_Label=SDCARD_CARD_DETECT
PC1.Signal=GPIO_Input
PC10.GPIOParameters=GPIO_Label
PC10.GPIO_Label=SPI_DISPLAY_SCK
PC10.Mode=TX_Only_Simplex_Unidirect_Master
PC10.Signal=SPI3_SCK
PC11.GPIOParameters=GPIO_Label
PC11.GPIO_Label=SPI_DISPLAY_MISO
PC11.Signal=SPI3_MISO
PC12.GPIOParameters=GPIO_Label
PC12.GPIO_Label=SPI_DISPLAY_MOSI
PC12.Mode=TX_Only_Simplex_Unidirect_Master
PC12.Signal=SPI3_MOSI
PC13.GPIOParameters=GPIO_Label
PC13.GPIO_Label=GPIO_15
PC13.Signal=GPIO_Output
PC14-OSC32_IN\ (OSC32_IN).GPIOParameters=GPIO_Label
PC14-OSC32_IN\ (OSC32_IN).GPIO_Label=GPIO_14
PC14-OSC32_IN\ (OSC32_IN).Signal=GPIO_Output
PC15-OSC32_OUT\ (OSC32_OUT).GPIOParameters=GPIO_Label
PC15-OSC32_OUT\ (OSC32_OUT).GPIO_Label=GPIO_13
PC15-OSC32_OUT\ (OSC32_OUT).Signal=GPIO_Output
PC2_C.GPIOParameters=GPIO_Label
PC2_C.GPIO_Label=SDCARD_SPI_MISO
PC2_C.Mode=Full_Duplex_Master
PC2_C.Signal=SPI2_MISO
PC3_C.GPIOParameters=GPIO_Label
PC3_C.GPIO_Label=SDCARD_SPI_MOSI
PC3_C.Mode=Full_Duplex_Master
PC3_C.Signal=SPI2_MOSI
PC4.GPIOParameters=GPIO_Label
PC4.GPIO_Label=ADC_00
PC4.Signal=ADCx_INP4
PC5.GPIOParameters=GPIO_Label
PC5.GPIO_Label=ADC_01
PC5.Signal=ADCx_INP8
PC6.GPIOParameters=GPIO_Label
PC6.GPIO_Label=LED_06
PC6.Signal=S_TIM8_CH1
PC7.GPIOParameters=GPIO_Label
PC7.GPIO_Label=LED_05
PC7.Signal=S_TIM8_CH2
PC8.GPIOParameters=GPIO_Label
PC8.GPIO_Label=LED_04
PC8.Signal=S_TIM8_CH3
PC9.GPIOParameters=GPIO_Label
PC9.GPIO_Label=LED_03
PC9.Signal=S_TIM8_CH4
PD0.GPIOParameters=GPIO_Label
PD0.GPIO_Label=SPI_DISPLAY_REGISTER_SELECT
PD0.Signal=GPIO_Output
PD1.GPIOParameters=GPIO_Label
PD1.GPIO_Label=SPI_DISPLAY_RESET
PD1.Signal=GPIO_Output
PD10.GPIOParameters=GPIO_Label
PD10.GPIO_Label=GPIO_05
PD10.Signal=GPIO_Output
PD11.GPIOParameters=GPIO_Label
PD11.GPIO_Label=GPIO_04
PD11.Signal=GPIO_Output
PD12.GPIOParameters=GPIO_Label
PD12.GPIO_Label=LED_10
PD12.Signal=S_TIM4_CH1
PD13.GPIOParameters=GPIO_Label
PD13.GPIO_Label=LED_09
PD13.Signal=S_TIM4_CH2
PD14.GPIOParameters=GPIO_Label
PD14.GPIO_Label=LED_08
PD14.Signal=S_TIM4_CH3
PD15.GPIOParameters=GPIO_Label
PD15.GPIO_Label=LED_07
PD15.Signal=S_TIM4_CH4
PD2.GPIOParameters=GPIO_Label
PD2.GPIO_Label=GPIO_03
PD2.Signal=GPIO_Output
PD3.GPIOParameters=GPIO_Label
PD3.GPIO_Label=GPIO_02
PD3.Signal=GPIO_Output
PD4.GPIOParameters=GPIO_Label
PD4.GPIO_Label=GPIO_01
PD4.Signal=GPIO_Output
PD5.GPIOParameters=GPIO_Label
PD5.GPIO_Label=SERIAL_DEBUG_TX
PD5.Mode=Asynchronous
PD5.Signal=USART2_TX
PD6.GPIOParameters=GPIO_Label
PD6.GPIO_Label=SERIAL_DEBUG_RX
PD6.Mode=Asynchronous
PD6.Signal=USART2_RX
PD7.GPIOParameters=GPIO_Label
PD7.GPIO_Label=GPIO_00
PD7.Signal=GPIO_Output
PD8.GPIOParameters=GPIO_Label
PD8.GPIO_Label=GPIO_07
PD8.Signal=GPIO_Output
PD9.GPIOParameters=GPIO_Label
PD9.GPIO_Label=GPIO_06
PD9.Signal=GPIO_Output
PE0.GPIOParameters=GPIO_Label
PE0.GPIO_Label=SERIAL_01_RX
PE0.Mode=Asynchronous
PE0.Signal=UART8_RX
PE1.GPIOParameters=GPIO_Label
PE1.GPIO_Label=SERIAL_01_TX
PE1.Mode=Asynchronous
PE1.Signal=UART8_TX
PE10.GPIOParameters=GPIO_Label
PE10.GPIO_Label=GPIO_09
PE10.Signal=GPIO_Output
PE11.GPIOParameters=GPIO_Label
PE11.GPIO_Label=SPI_USR_CS
PE11.Mode=NSS_Signal_Hard_Output
PE11.Signal=SPI4_NSS
PE12.GPIOParameters=GPIO_Label
PE12.GPIO_Label=SPI_USR_SCK
PE12.Mode=Full_Duplex_Master
PE12.Signal=SPI4_SCK
PE13.GPIOParameters=GPIO_Label
PE13.GPIO_Label=SPI_USR_MISO
PE13.Mode=Full_Duplex_Master
PE13.Signal=SPI4_MISO
PE14.GPIOParameters=GPIO_Label
PE14.GPIO_Label=SPI_USR_MOSI
PE14.Mode=Full_Duplex_Master
PE14.Signal=SPI4_MOSI
PE15.GPIOParameters=GPIO_Label
PE15.GPIO_Label=GPIO_08
PE15.Signal=GPIO_Output
PE2.GPIOParameters=GPIO_Label
PE2.GPIO_Label=AUDIOCODEC_SAI1_MCLK_A
PE2.Mode=SAI_A_MasterWithClock
PE2.Signal=SAI1_MCLK_A
PE3.GPIOParameters=GPIO_Label
PE3.GPIO_Label=AUDIOCODEC_SAI1_SD_B
PE3.Mode=SAI_B_SyncSlave
PE3.Signal=SAI1_SD_B
PE4.GPIOParameters=GPIO_Label
PE4.GPIO_Label=AUDIOCODEC_SAI1_FS_A
PE4.Mode=SAI_A_MasterWithClock
PE4.Signal=SAI1_FS_A
PE5.GPIOParameters=GPIO_Label
PE5.GPIO_Label=AUDIOCODEC_SAI1_SCK_A
PE5.Mode=SAI_A_MasterWithClock
PE5.Signal=SAI1_SCK_A
PE6.GPIOParameters=GPIO_Label
PE6.GPIO_Label=AUDIOCODEC_SAI1_SD_A
PE6.Mode=SAI_A_MasterWithClock
PE6.Signal=SAI1_SD_A
PE7.GPIOParameters=GPIO_Label
PE7.GPIO_Label=SERIAL_00_RX
PE7.Mode=Asynchronous
PE7.Signal=UART7_RX
PE8.GPIOParameters=GPIO_Label
PE8.GPIO_Label=SERIAL_00_TX
PE8.Mode=Asynchronous
PE8.Signal=UART7_TX
PE9.GPIOParameters=GPIO_Label
PE9.GPIO_Label=GPIO_10
PE9.Signal=GPIO_Output
PH0-OSC_IN\ (PH0).GPIOParameters=GPIO_Label
PH0-OSC_IN\ (PH0).GPIO_Label=RCC_OSC_IN
PH0-OSC_IN\ (PH0).Mode=HSE-External-Oscillator
PH0-OSC_IN\ (PH0).Signal=RCC_OSC_IN
PH1-OSC_OUT\ (PH1).GPIOParameters=GPIO_Label
PH1-OSC_OUT\ (PH1).GPIO_Label=RCC_OSC_OUT
PH1-OSC_OUT\ (PH1).Mode=HSE-External-Oscillator
PH1-OSC_OUT\ (PH1).Signal=RCC_OSC_OUT
RCC.HSE_VALUE=16000000
RCC.SYSCLKFreq_VALUE=480000000
RCC.SYSCLKSource=RCC_SYSCLKSOURCE_PLLCLK
board=custom

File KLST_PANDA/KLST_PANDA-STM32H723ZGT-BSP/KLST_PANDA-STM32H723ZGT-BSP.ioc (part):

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Mcu.Name=STM32H723ZGTx
Mcu.Package=LQFP144
Mcu.UserName=STM32H723ZGTx
PA0.GPIOParameters=GPIO_Label
PA0.GPIO_Label=ENCODER_01_A
PA0.Signal=S_TIM2_CH1_ETR
PA1.Mode=RGB888
PA1.Signal=LTDC_R2
PA10.GPIOParameters=GPIO_Label
PA10.GPIO_Label=ENCODER_00_BUTTON
PA10.Signal=S_TIM1_CH3
PA11.GPIOParameters=GPIO_Label
PA11.GPIO_Label=USB_DEVICE_HOST_MINUS
PA11.Mode=Host_FS
PA11.Signal=USB_OTG_HS_DM
PA12.GPIOParameters=GPIO_Label
PA12.GPIO_Label=USB_DEVICE_HOST_PLUS
PA12.Mode=Host_FS
PA12.Signal=USB_OTG_HS_DP
PA13(JTMS/SWDIO).GPIOParameters=GPIO_Label
PA13(JTMS/SWDIO).GPIO_Label=SWD_IO
PA13(JTMS/SWDIO).Mode=Serial_Wire
PA13(JTMS/SWDIO).Signal=DEBUG_JTMS-SWDIO
PA14(JTCK/SWCLK).GPIOParameters=GPIO_Label
PA14(JTCK/SWCLK).GPIO_Label=SWD_CLK
PA14(JTCK/SWCLK).Mode=Serial_Wire
PA14(JTCK/SWCLK).Signal=DEBUG_JTCK-SWCLK
PA15(JTDI).Mode=RGB888
PA15(JTDI).Signal=LTDC_R3
PA2.Mode=RGB888
PA2.Signal=LTDC_R1
PA3.Mode=RGB888
PA3.Signal=LTDC_B2
PA4.GPIOParameters=GPIO_Label
PA4.GPIO_Label=DAC_00
PA4.Signal=COMP_DAC11_group
PA5.Mode=RGB888
PA5.Signal=LTDC_R4
PA6.Mode=RGB888
PA6.Signal=LTDC_G2
PA7.Mode=RGB888
PA7.Signal=LTDC_VSYNC
PA8.Mode=RGB888
PA8.Signal=LTDC_R6
PA9.GPIOParameters=GPIO_Label
PA9.GPIO_Label=USB_DEVICE_HOST_VBUS
PA9.Mode=Activate_VBUS_FS
PA9.Signal=USB_OTG_HS_VBUS
PB0.Mode=OCTOSPI1_IOL_Port1L
PB0.Signal=OCTOSPIM_P1_IO1
PB1.Mode=RGB888
PB1.Signal=LTDC_G0
PB10.Mode=RGB888
PB10.Signal=LTDC_G4
PB11.GPIOParameters=GPIO_Label
PB11.GPIO_Label=ENCODER_01_BUTTON
PB11.Signal=S_TIM2_CH4
PB12.Mode=OCTOSPI1_IOL_Port1L
PB12.Signal=OCTOSPIM_P1_IO0
PB13.Mode=OCTOSPI1_IOL_Port1L
PB13.Signal=OCTOSPIM_P1_IO2
PB14.GPIOParameters=GPIO_Label
PB14.GPIO_Label=GPIO_PWM_02
PB14.Signal=S_TIM12_CH1
PB15.GPIOParameters=GPIO_Label
PB15.GPIO_Label=SPI_01_MOSI
PB15.Mode=Full_Duplex_Master
PB15.Signal=SPI2_MOSI
PB2.GPIOParameters=GPIO_Label
PB2.GPIO_Label=AUDIOCODEC_00_SD_A
PB2.Mode=SAI_A_SyncSlave
PB2.Signal=SAI1_SD_A
PB3(JTDO/TRACESWO).GPIOParameters=GPIO_Label
PB3(JTDO/TRACESWO).GPIO_Label=ENCODER_01_B
PB3(JTDO/TRACESWO).Signal=S_TIM2_CH2
PB4(NJTRST).GPIOParameters=GPIO_Label
PB4(NJTRST).GPIO_Label=SPI_01_CS
PB4(NJTRST).Mode=NSS_Signal_Hard_Output
PB4(NJTRST).Signal=SPI2_NSS
PB5.Mode=RGB888
PB5.Signal=LTDC_B5
PB6.GPIOParameters=GPIO_Label
PB6.GPIO_Label=I2C_00_SCL
PB6.Mode=I2C
PB6.Signal=I2C1_SCL
PB7.GPIOParameters=GPIO_Label
PB7.GPIO_Label=I2C_00_SDA
PB7.Mode=I2C
PB7.Signal=I2C1_SDA
PB8.Mode=RGB888
PB8.Signal=LTDC_B6
PB9.Mode=RGB888
PB9.Signal=LTDC_B7
PC0.Mode=RGB888
PC0.Signal=LTDC_R5
PC1.Mode=RGB888
PC1.Signal=LTDC_G5
PC10.GPIOParameters=GPIO_Label
PC10.GPIO_Label=CARD_SDMMC_D2
PC10.Mode=SD_4_bits_Wide_bus
PC10.Signal=SDMMC1_D2
PC11.GPIOParameters=GPIO_Label
PC11.GPIO_Label=CARD_SDMMC_D3
PC11.Mode=SD_4_bits_Wide_bus
PC11.Signal=SDMMC1_D3
PC12.GPIOParameters=GPIO_Label
PC12.GPIO_Label=CARD_SDMMC_CK
PC12.Mode=SD_4_bits_Wide_bus
PC12.Signal=SDMMC1_CK
PC2_C.GPIOParameters=GPIO_Label
PC2_C.GPIO_Label=SPI_01_MISO
PC2_C.Mode=Full_Duplex_Master
PC2_C.Signal=SPI2_MISO
PC3_C.GPIOParameters=GPIO_Label
PC3_C.GPIO_Label=ADC_02
PC3_C.Mode=IN1-Single-Ended
PC3_C.Signal=ADC3_INP1
PC4.GPIOParameters=GPIO_Label
PC4.GPIO_Label=ADC_00
PC4.Signal=ADCx_INP4
PC5.Mode=OCTOSPI1_Port1_DQS
PC5.Signal=OCTOSPIM_P1_DQS
PC6.Mode=RGB888
PC6.Signal=LTDC_HSYNC
PC7.Mode=RGB888
PC7.Signal=LTDC_G6
PC8.GPIOParameters=GPIO_Label
PC8.GPIO_Label=CARD_SDMMC_D0
PC8.Mode=SD_4_bits_Wide_bus
PC8.Signal=SDMMC1_D0
PC9.GPIOParameters=GPIO_Label
PC9.GPIO_Label=CARD_SDMMC_D1
PC9.Mode=SD_4_bits_Wide_bus
PC9.Signal=SDMMC1_D1
PD0.Mode=RGB888
PD0.Signal=LTDC_B1
PD10.Mode=RGB888
PD10.Signal=LTDC_B3
PD11.GPIOParameters=GPIO_Label
PD11.GPIO_Label=AUDIOCODEC_01_SD_A
PD11.Mode=SAI_A_MasterWithClock
PD11.Signal=SAI4_SD_A
PD12.GPIOParameters=GPIO_Label
PD12.GPIO_Label=AUDIOCODEC_01_FS_A
PD12.Mode=SAI_A_MasterWithClock
PD12.Signal=SAI4_FS_A
PD13.GPIOParameters=GPIO_Label
PD13.GPIO_Label=AUDIOCODEC_01_SCK_A
PD13.Mode=SAI_A_MasterWithClock
PD13.Signal=SAI4_SCK_A
PD14.GPIOParameters=GPIO_Label
PD14.GPIO_Label=GPIO_PWM_01
PD14.Signal=S_TIM4_CH3
PD15.GPIOParameters=GPIO_Label
PD15.GPIO_Label=GPIO_PWM_00
PD15.Signal=S_TIM4_CH4
PD2.GPIOParameters=GPIO_Label
PD2.GPIO_Label=CARD_SDMMC_CMD
PD2.Mode=SD_4_bits_Wide_bus
PD2.Signal=SDMMC1_CMD
PD3.GPIOParameters=GPIO_Label
PD3.GPIO_Label=SPI_01_SCK
PD3.Mode=Full_Duplex_Master
PD3.Signal=SPI2_SCK
PD5.GPIOParameters=GPIO_Label
PD5.GPIO_Label=SERIAL_DEBUG_TX
PD5.Mode=Asynchronous
PD5.Signal=USART2_TX
PD6.GPIOParameters=GPIO_Label
PD6.GPIO_Label=SERIAL_DEBUG_RX
PD6.Mode=Asynchronous
PD6.Signal=USART2_RX
PD8.GPIOParameters=GPIO_Label
PD8.GPIO_Label=SERIAL_00_TX
PD8.Mode=Asynchronous
PD8.Signal=USART3_TX
PD9.GPIOParameters=GPIO_Label
PD9.GPIO_Label=SERIAL_00_RX
PD9.Mode=Asynchronous
PD9.Signal=USART3_RX
PE0.GPIOParameters=GPIO_Label
PE0.GPIO_Label=SERIAL_01_RX
PE0.Mode=Asynchronous
PE0.Signal=UART8_RX
PE1.GPIOParameters=GPIO_Label
PE1.GPIO_Label=SERIAL_01_TX
PE1.Mode=Asynchronous
PE1.Signal=UART8_TX
PE10.Mode=OCTOSPI1_IOH_Port1H
PE10.Signal=OCTOSPIM_P1_IO7
PE11.GPIOParameters=GPIO_Label
PE11.GPIO_Label=ENCODER_00_B
PE11.Signal=S_TIM1_CH2
PE12.GPIOParameters=GPIO_Label
PE12.GPIO_Label=SPI_00_SCK
PE12.Mode=Full_Duplex_Master
PE12.Signal=SPI4_SCK
PE13.Mode=RGB888
PE13.Signal=LTDC_DE
PE14.GPIOParameters=GPIO_Label
PE14.GPIO_Label=SPI_00_MOSI
PE14.Mode=Full_Duplex_Master
PE14.Signal=SPI4_MOSI
PE15.Mode=RGB888
PE15.Signal=LTDC_R7
PE2.GPIOParameters=GPIO_Label
PE2.GPIO_Label=AUDIOCODEC_01_MCLK_A
PE2.Mode=SAI_A_MasterWithClock
PE2.Signal=SAI4_MCLK_A
PE3.GPIOParameters=GPIO_Label
PE3.GPIO_Label=AUDIOCODEC_00_SD_B
PE3.Mode=SAI_B_MasterWithClock
PE3.Signal=SAI1_SD_B
PE4.GPIOParameters=GPIO_Label
PE4.GPIO_Label=SPI_00_CS
PE4.Mode=NSS_Signal_Hard_Output
PE4.Signal=SPI4_NSS
PE5.GPIOParameters=GPIO_Label
PE5.GPIO_Label=SPI_00_MISO
PE5.Mode=Full_Duplex_Master
PE5.Signal=SPI4_MISO
PE6.Mode=RGB888
PE6.Signal=LTDC_G1
PE7.Mode=OCTOSPI1_IOH_Port1H
PE7.Signal=OCTOSPIM_P1_IO4
PE8.Mode=OCTOSPI1_IOH_Port1H
PE8.Signal=OCTOSPIM_P1_IO5
PE9.GPIOParameters=GPIO_Label
PE9.GPIO_Label=ENCODER_00_A
PE9.Signal=S_TIM1_CH1
PF0.GPIOParameters=GPIO_Label
PF0.GPIO_Label=GPIO_PWM_03
PF0.Mode=PWM Generation1 CH1
PF0.Signal=TIM23_CH1
PF1.GPIOParameters=GPIO_Label
PF1.GPIO_Label=GPIO_PWM_04
PF1.Signal=S_TIM23_CH2
PF10.Mode=O1_P1_CLK
PF10.Signal=OCTOSPIM_P1_CLK
PF11.GPIOParameters=GPIO_Label
PF11.GPIO_Label=AUDIOCODEC_01_SD_B
PF11.Mode=SAI_B_SyncSlave
PF11.Signal=SAI4_SD_B
PF12.GPIOParameters=GPIO_Label
PF12.GPIO_Label=GPIO_PWM_07
PF12.Signal=S_TIM24_CH2
PF13.GPIOParameters=GPIO_Label
PF13.GPIO_Label=ADC_01
PF13.Mode=IN2-Single-Ended
PF13.Signal=ADC2_INP2
PF14.GPIOParameters=GPIO_Label
PF14.GPIO_Label=I2C_01_SCL
PF14.Mode=I2C
PF14.Signal=I2C4_SCL
PF15.GPIOParameters=GPIO_Label
PF15.GPIO_Label=I2C_01_SDA
PF15.Mode=I2C
PF15.Signal=I2C4_SDA
PF2.GPIOParameters=GPIO_Label
PF2.GPIO_Label=GPIO_PWM_05
PF2.Signal=S_TIM23_CH3
PF3.GPIOParameters=GPIO_Label
PF3.GPIO_Label=GPIO_PWM_06
PF3.Signal=S_TIM23_CH4
PF6.Mode=OCTOSPI1_IOL_Port1L
PF6.Signal=OCTOSPIM_P1_IO3
PF7.GPIOParameters=GPIO_Label
PF7.GPIO_Label=AUDIOCODEC_00_MCLK_B
PF7.Mode=SAI_B_MasterWithClock
PF7.Signal=SAI1_MCLK_B
PF8.GPIOParameters=GPIO_Label
PF8.GPIO_Label=AUDIOCODEC_00_SCK_B
PF8.Mode=SAI_B_MasterWithClock
PF8.Signal=SAI1_SCK_B
PF9.GPIOParameters=GPIO_Label
PF9.GPIO_Label=AUDIOCODEC_00_FS_B
PF9.Mode=SAI_B_MasterWithClock
PF9.Signal=SAI1_FS_B
PG0.GPIOParameters=GPIO_Label
PG0.GPIO_Label=SERIAL_02_RX
PG0.Mode=Asynchronous
PG0.Signal=UART9_RX
PG1.GPIOParameters=GPIO_Label
PG1.GPIO_Label=SERIAL_02_TX
PG1.Mode=Asynchronous
PG1.Signal=UART9_TX
PG10.Mode=RGB888
PG10.Signal=LTDC_G3
PG12.Mode=RGB888
PG12.Signal=LTDC_B4
PG13.Mode=RGB888
PG13.Signal=LTDC_R0
PG14.Mode=RGB888
PG14.Signal=LTDC_B0
PG6.Mode=OCTOSPI1_Port1_NCS
PG6.Signal=OCTOSPIM_P1_NCS
PG7.Mode=RGB888
PG7.Signal=LTDC_CLK
PG8.Mode=RGB888
PG8.Signal=LTDC_G7
PG9.Mode=OCTOSPI1_IOH_Port1H
PG9.Signal=OCTOSPIM_P1_IO6
PH0-OSC_IN.GPIOParameters=GPIO_Label
PH0-OSC_IN.GPIO_Label=RCC_OSC_IN
PH0-OSC_IN.Mode=HSE-External-Oscillator
PH0-OSC_IN.Signal=RCC_OSC_IN
PH1-OSC_OUT.GPIOParameters=GPIO_Label
PH1-OSC_OUT.GPIO_Label=RCC_OSC_OUT
PH1-OSC_OUT.Mode=HSE-External-Oscillator
PH1-OSC_OUT.Signal=RCC_OSC_OUT
RCC.HSE_VALUE=8000000
RCC.SYSCLKFreq_VALUE=550000000
RCC.SYSCLKSource=RCC_SYSCLKSOURCE_PLLCLK
board=custom
